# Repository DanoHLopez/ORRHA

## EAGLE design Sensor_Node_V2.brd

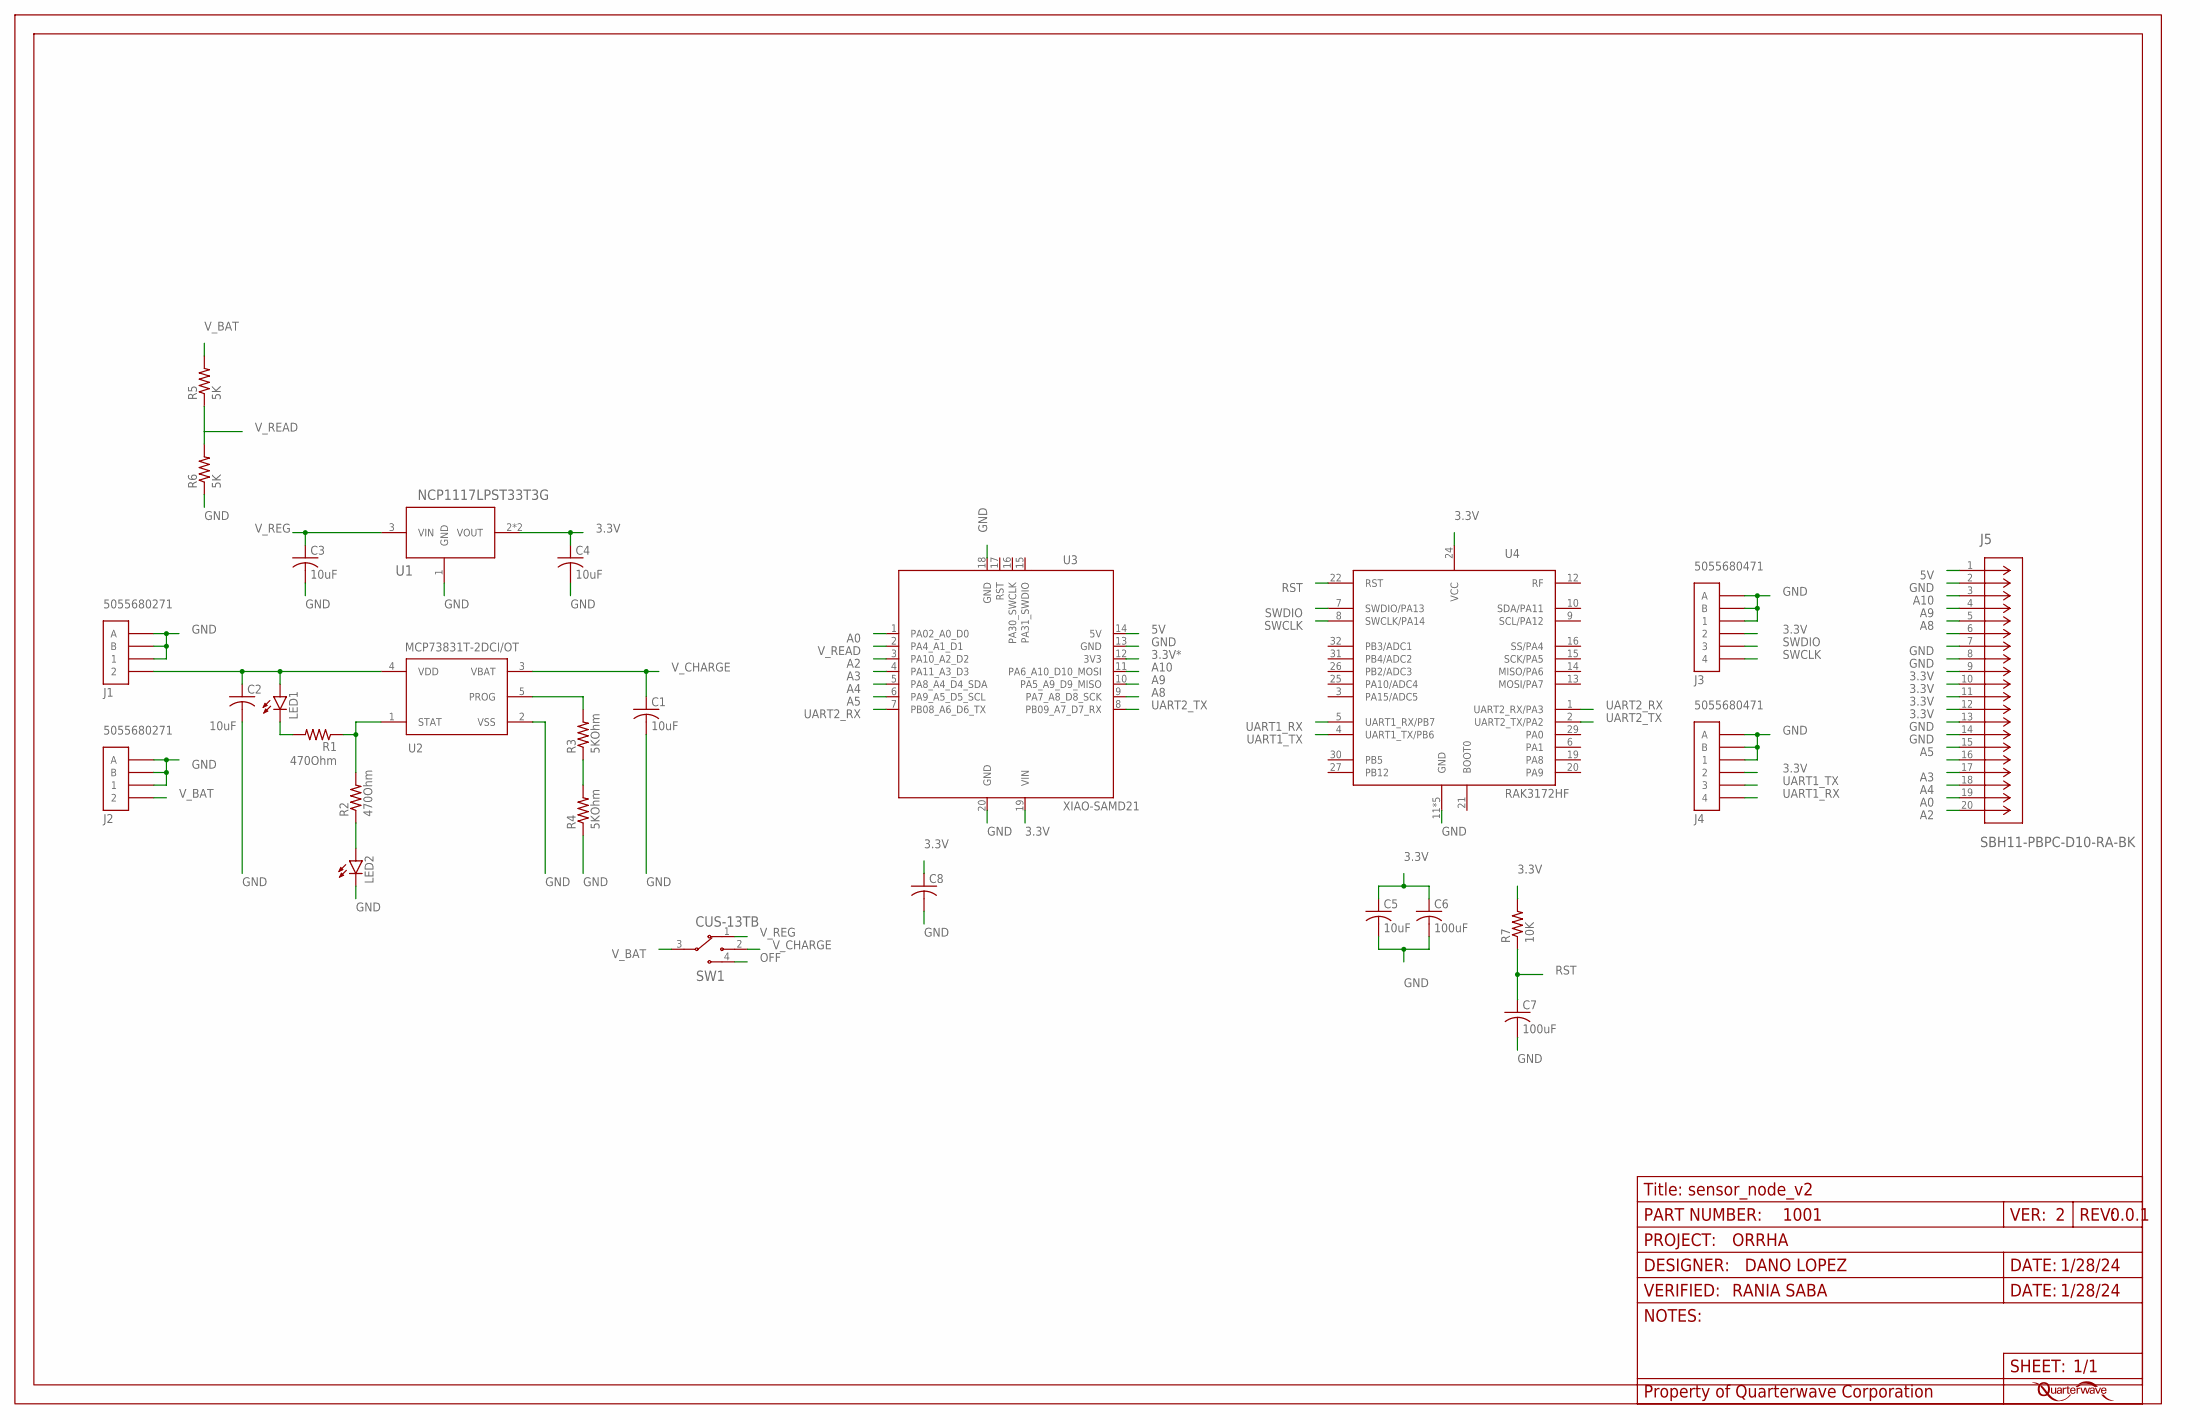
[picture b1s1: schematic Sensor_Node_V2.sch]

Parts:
C1, C2, C3, C4, C5: 10uF; C0805
C6, C7: 100uF; C0805
C8: C-USC0805; C0805
FRAME1: STANDARDSTD_INFO_HW14_W30; STD_INFO_H14_W30; PART_NUMBER 1001
J1, J2: 5055680271
J3, J4: 5055680471
J5: SBH11-PBPC-D10-RA-BK; CONN20_D10-RA-BK_SUL
LED1, LED2: LEDCHIPLED_0603; CHIPLED_0603
R1, R2: 470Ohm; R0805
R3, R4: 5KOhm; R0805
R5, R6: 5K; R0805
R7: 10K; R0805
SW1: CUS-13TB; CUS-13TB_NDC
U1: NCP1117LPST33T3G; SOT-223_DIO
U2: MCP73831T-2DCI/OT; SOT-23-5_MC_MCH
U3: XIAO-SAMD21; XIAO-SAMD21/RP2040-MODULE14P-2.54-21X17.8MM
U4: RAK3172HF; RAK3172

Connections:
3.3V: C4.1, C5.1, C6.1, C8.1, J3.2, J4.2, J5.9, J5.10, J5.11, J5.12, R7.2, U1.2 (VOUT), U1.4 (VOUT), U3.19 (VIN), U4.24 (VCC)
3.3V*: U3.12 (3V3)
5V: J5.1, U3.14 (5V)
A0: J5.19, U3.1 (PA02_A0_D0)
A2: J5.20, U3.3 (PA10_A2_D2)
A3: J5.17, U3.4 (PA11_A3_D3)
A4: J5.18, U3.5 (PA8_A4_D4_SDA)
A5: J5.15, U3.6 (PA9_A5_D5_SCL)
A8: J5.5, U3.9 (PA7_A8_D8_SCK)
A9: J5.4, U3.10 (PA5_A9_D9_MISO)
A10: J5.3, U3.11 (PA6_A10_D10_MOSI)
GND: C1.2, C2.2, C3.2, C4.2, C5.2, C6.2, C7.2, C8.2, J1.1, J1.A, J1.B, J2.1, J2.A, J2.B, J3.1, J3.A, J3.B, J4.1, J4.A, J4.B, J5.2, J5.7, J5.8, J5.13, J5.14, LED2.C, R4.1, R6.1, U1.1 (GND), U2.2 (VSS), U3.13 (GND), U3.18 (GND), U3.20 (GND), U4.11 (GND), U4.17 (GND), U4.18 (GND), U4.23 (GND), U4.28 (GND)
unnamed: LED1.C, R1.2
unnamed: R1.1, R2.2, U2.1 (STAT)
unnamed: R3.2, U2.5 (PROG)
unnamed: R3.1, R4.2
unnamed: LED2.A, R2.1
unnamed: C2.1, J1.2, LED1.A, U2.4 (VDD)
OFF: SW1.4
RST: C7.1, R7.1, U4.22 (RST)
SWCLK: J3.4, U4.8 (SWCLK/PA14)
SWDIO: J3.3, U4.7 (SWDIO/PA13)
UART1_RX: J4.4, U4.5 (UART1_RX/PB7)
UART1_TX: J4.3, U4.4 (UART1_TX/PB6)
UART2_RX: U3.7 (PB08_A6_D6_TX), U4.1 (UART2_RX/PA3)
UART2_TX: U3.8 (PB09_A7_D7_RX), U4.2 (UART2_TX/PA2)
V_BAT: J2.2, R5.2, SW1.3
V_CHARGE: C1.1, SW1.2, U2.3 (VBAT)
V_READ: R5.1, R6.2, U3.2 (PA4_A1_D1)
V_REG: C3.1, SW1.1, U1.3 (VIN)

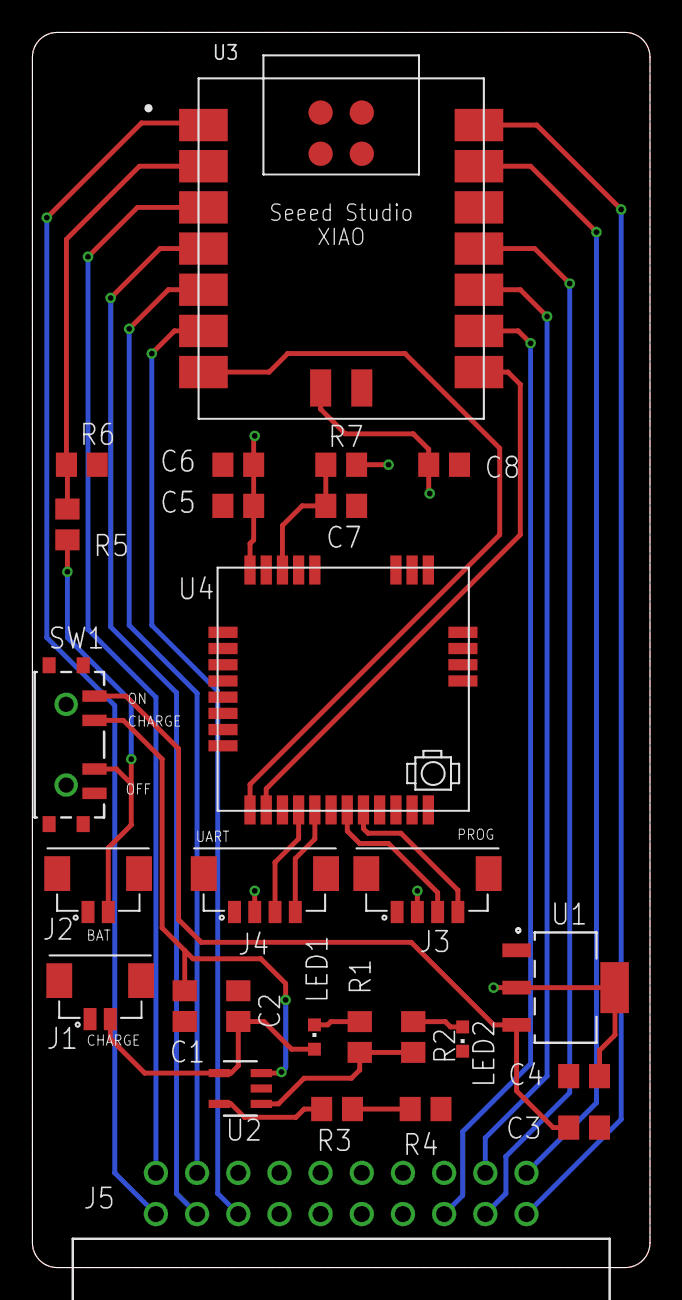
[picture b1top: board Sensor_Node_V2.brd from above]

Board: 2 copper layers, 38.1 x 76.2 mm, 28 parts (1 on the bottom side), 28 nets.

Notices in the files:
parts and their libraries:
COPYRIGHT: Copyright (C) 2024 Ultra Librarian. All rights reserved.
COPYRIGHT: Copyright (C) 2021 Ultra Librarian. All rights reserved.
COPYRIGHT: Copyright (C) 2022 Ultra Librarian. All rights reserved.
